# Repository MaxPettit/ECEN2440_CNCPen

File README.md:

# ECEN2440_CNCPen (Joy Pen)
CNC Joystick Pen for ECEN2440 Final

Efram Aredo, Nathan Elsen, Max Pettit

See the hackster.io post for more details [here](https://www.hackster.io/maxpettit/joy-pen-74b8a4).

Brief Explanation of files below

## adc 
* Initializes analog to digital conversion: sets ADC14 sample-and-hold times, starts ADC sample conversions, turns on ADC14
* Captures values and outputs them

## gpio 
* Initializes pins on MSP inorder to configure motor driver boards
* Initializes things like step size, enable, stepper mode

## led_test
* Used in testing ADC and joystick.
* On board LED will change color depending on position of joystick

## main 
* Calls config and init functions
* Endless loop which reads joystick values and moves motors accordingly

## motor
* Starts and stops motor pwm based on joystick position
* Determines direction of motors based on joystick position

## pwm 
* Configures timers to create pulse width modulations
* PWM outputs used to move motors and servo
* Can be paused

## read_js
* Configures xout and yout pins on the joystick to MSP pins for ADC reading
* Takes in ADC reading and output the joystick position

## uart_driver
* Configures and initializes eUSCI for UART communication to LCD
* Writes desired messages to LCD

## up_start
* Calls config functions and starts timers
* Displays start up message

## z_driver
* Configures pin to trigger interrupt on falling edge which corresponds to a joystick click
* Enables necessary interrupt
* On interrupt, toggles the pen position (up/down)
* Sets pen position by changing duty cycle of pwm wave to servo

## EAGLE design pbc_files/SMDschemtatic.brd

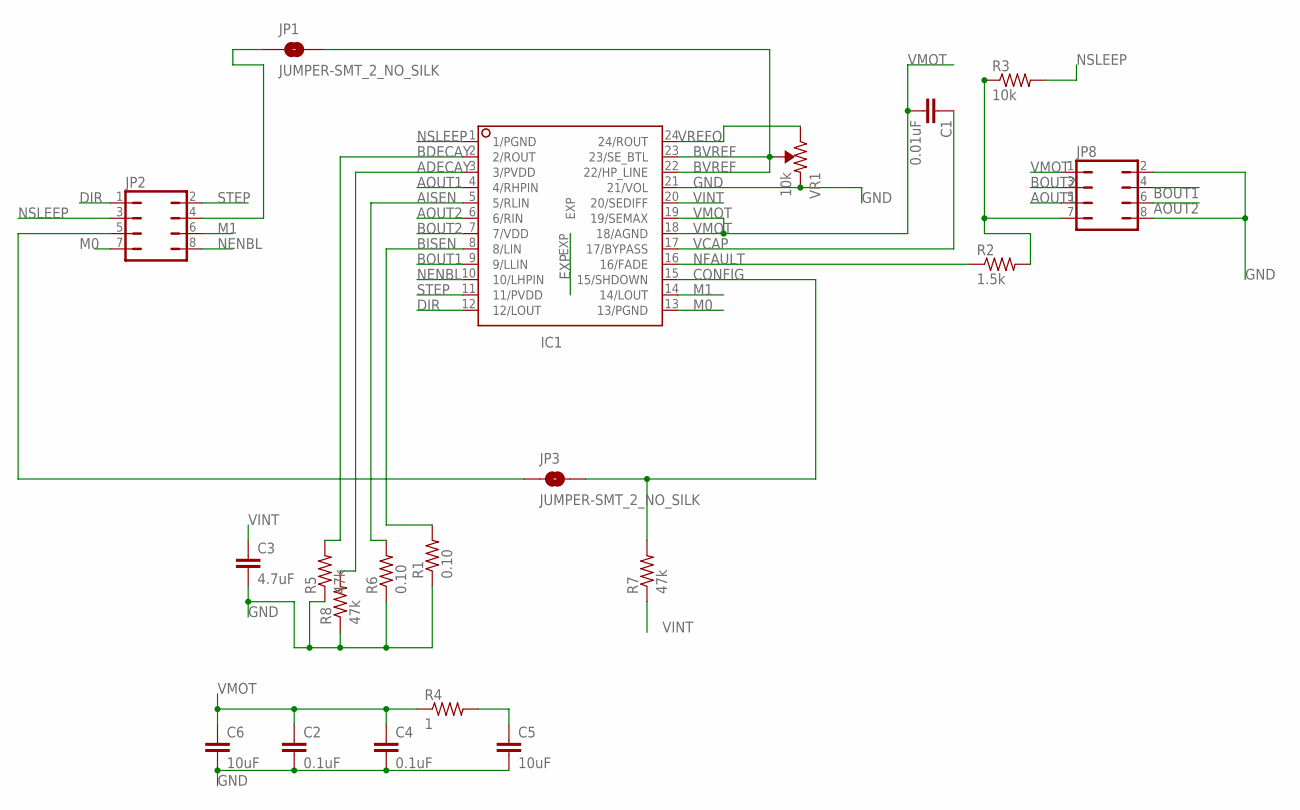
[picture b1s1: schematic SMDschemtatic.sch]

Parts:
C1: 0.01uF; 0603
C2, C4: 0.1uF; 0603
C3: 4.7uF; 0603
C5, C6: 10uF; 0603
IC1: PA3011; HTSSOP24
JP1, JP3: JUMPER-SMT_2_NO_SILK; SMT-JUMPER_2_NO_SILK
JP2, JP8: JP4Q
R1, R6: 0.10; R2512
R2: 1.5k; R2512
R3: 10k; R2512
R4: 1; R2512
R5, R7, R8: 47k; R2512
VR1: 10k; TRIMPOT-SMD-3MM-CLOSED

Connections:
ADECAY: IC1.3 (3/PVDD), R8.2
AISEN: IC1.5 (5/RLIN), R6.2
AOUT1: IC1.4 (4/RHPIN), JP8.5
AOUT2: IC1.6 (6/RIN), JP8.6
BDECAY: IC1.2 (2/ROUT), R5.2
BISEN: IC1.8 (8/LIN), R1.2
BOUT1: IC1.9 (9/LLIN), JP8.4
BOUT2: IC1.7 (7/VDD), JP8.3
BVREF: IC1.22 (22/HP_LINE), IC1.23 (23/SE_BTL), JP1.2, VR1.2 (WIPER)
CONFIG: IC1.15 (15/SHDOWN), JP3.2, R7.2
DIR: IC1.12 (12/LOUT), JP2.1
EXP: IC1.EXP
GND: C2.2, C3.2, C4.2, C5.2, C6.2, IC1.21 (21/VOL), JP8.2, JP8.8, R1.1, R5.1, R6.1, R8.1, VR1.1 (CCW)
M0: IC1.13 (13/PGND), JP2.7
M1: IC1.14 (14/LOUT), JP2.6
unnamed: JP2.5, JP3.1
unnamed: JP8.7, R2.2, R3.1
unnamed: JP1.1, JP2.4
unnamed: C5.1, R4.2
NENBL: IC1.10 (10/LHPIN), JP2.8
NFAULT: IC1.16 (16/FADE), R2.1
NSLEEP: IC1.1 (1/PGND), JP2.3, R3.2
STEP: IC1.11 (11/PVDD), JP2.2
VCAP: C1.1, IC1.17 (17/BYPASS)
VINT: C3.1, IC1.20 (20/SEDIFF), R7.1
VMOT: C1.2, C2.1, C4.1, C6.1, IC1.18 (18/AGND), IC1.19 (19/SEMAX), JP8.1, R4.1
VREFO: IC1.24 (24/ROUT), VR1.3 (CW)

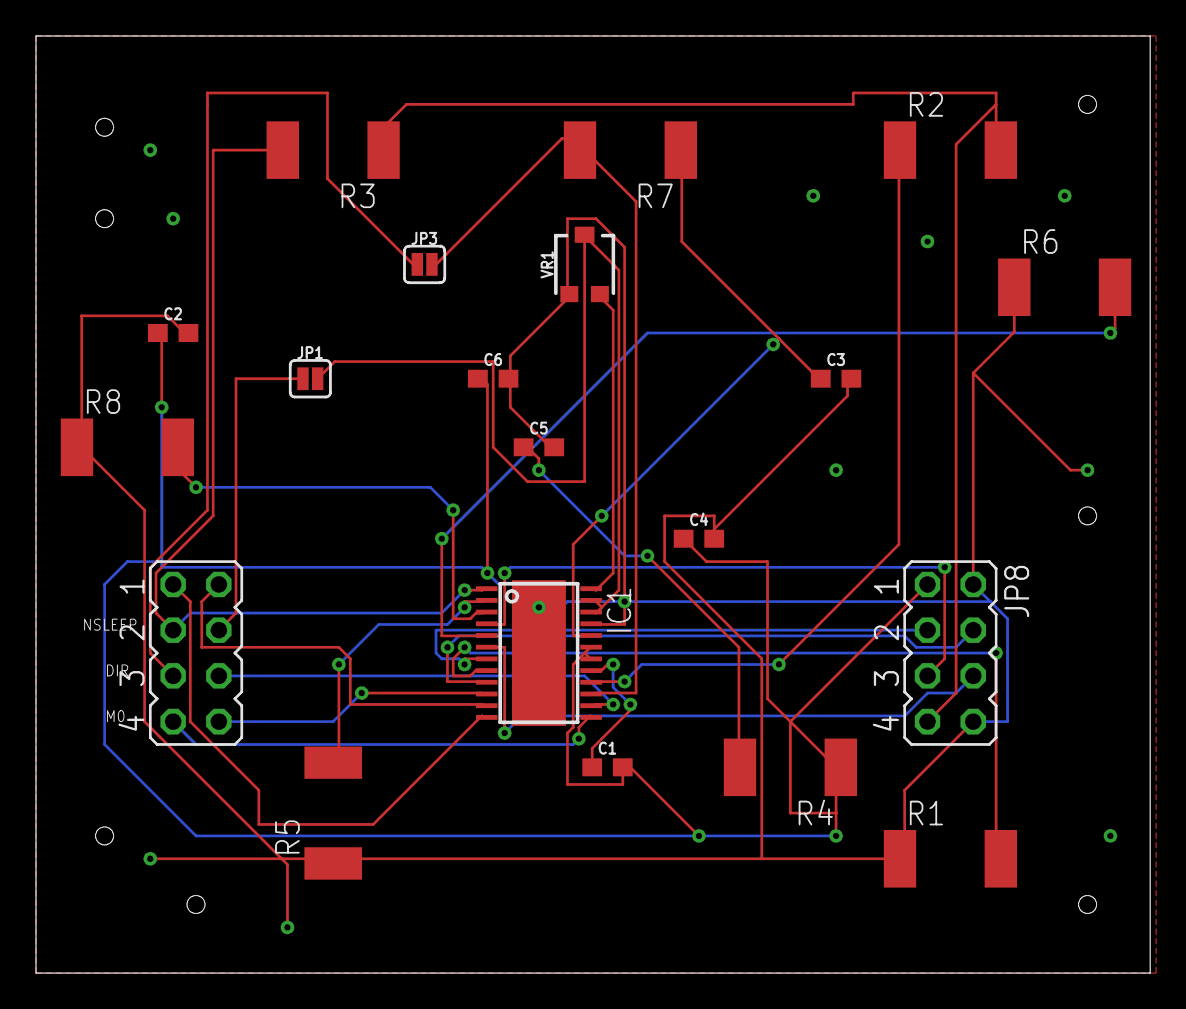
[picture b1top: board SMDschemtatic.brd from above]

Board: 2 copper layers, 61.9 x 52.1 mm, 20 parts (0 on the bottom side), 26 nets.

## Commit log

2019-12-17 Create d

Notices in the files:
parts and their libraries:
SparkFun-Capacitors: Licensing: Creative Commons ShareAlike 4.0 International - https://creativecommons.org/licenses/by-sa/4.0
